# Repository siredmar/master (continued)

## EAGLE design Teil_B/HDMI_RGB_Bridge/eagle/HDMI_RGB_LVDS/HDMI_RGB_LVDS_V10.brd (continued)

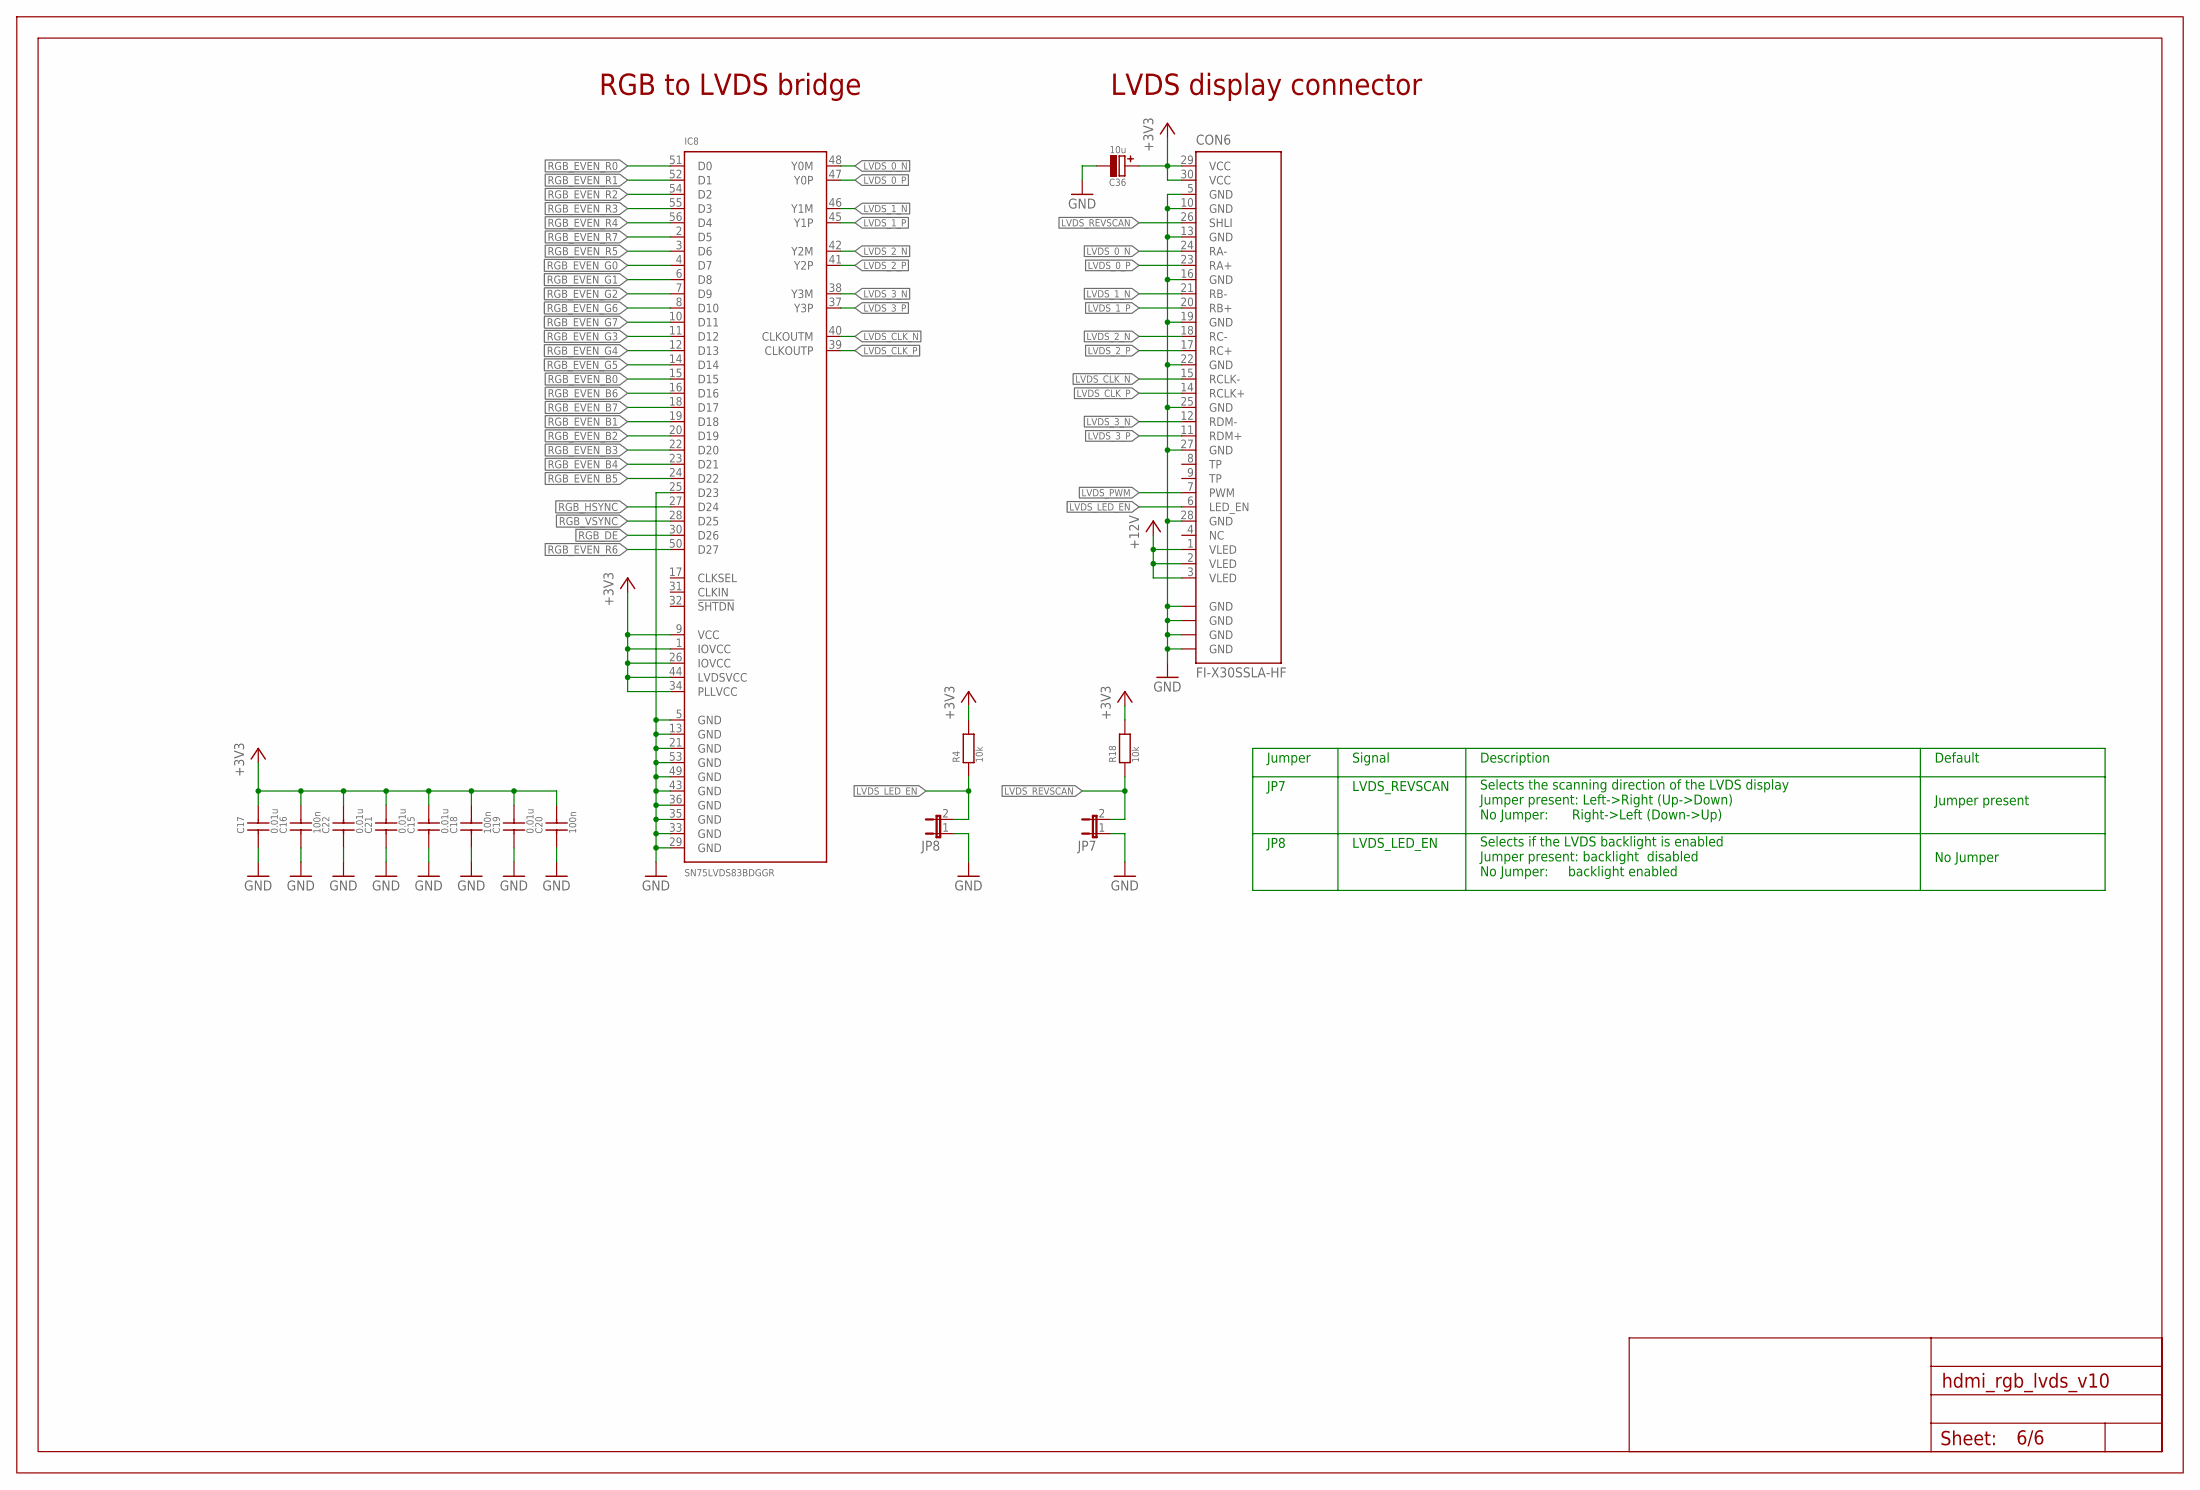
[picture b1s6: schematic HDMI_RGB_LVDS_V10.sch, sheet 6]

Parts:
C15, C17, C19, C21, C22: 0.01u; C0402
C16, C18, C20: 100n; C0402
C36: 10u; C_POL_4X4MM
CON6: FI-X30SSLA-HF
IC8: SN75LVDS83BDGGR; TSSOP-56
JP7, JP8: JUMPER2; JUMPER2_THROUGHHOLE
R4, R18: 10k; R0402
U$5: FRAME_A3_LANDSCAPE; FRAME

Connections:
+3V3: C15.2, C16.2, C17.2, C18.2, C19.2, C20.2, C21.2, C22.2, C36.+, CON6.29 (VCC), CON6.30 (VCC), IC8.1 (IOVCC), IC8.9 (VCC), IC8.26 (IOVCC), IC8.34 (PLLVCC), IC8.44 (LVDSVCC), R4.2, R18.2; also elsewhere on the board
+12V: CON6.1 (VLED), CON6.2 (VLED), CON6.3 (VLED); also elsewhere on the board
GND: C15.1, C16.1, C17.1, C18.1, C19.1, C20.1, C21.1, C22.1, C36.-, CON6.5 (GND), CON6.10 (GND), CON6.13 (GND), CON6.16 (GND), CON6.19 (GND), CON6.22 (GND), CON6.25 (GND), CON6.27 (GND), CON6.28 (GND), CON6.GND@1 (GND), CON6.GND@2 (GND), CON6.GND@3 (GND), CON6.GND@4 (GND), IC8.5 (GND), IC8.13 (GND), IC8.21 (GND), IC8.25 (D23), IC8.29 (GND), IC8.33 (GND), IC8.35 (GND), IC8.36 (GND), IC8.43 (GND), IC8.49 (GND), IC8.53 (GND), JP7.1, JP8.1; also elsewhere on the board
LVDS_0_N: CON6.24 (RA-), IC8.48 (Y0M)
LVDS_0_P: CON6.23 (RA+), IC8.47 (Y0P)
LVDS_1_N: CON6.21 (RB-), IC8.46 (Y1M)
LVDS_1_P: CON6.20 (RB+), IC8.45 (Y1P)
LVDS_2_N: CON6.18 (RC-), IC8.42 (Y2M)
LVDS_2_P: CON6.17 (RC+), IC8.41 (Y2P)
LVDS_3_N: CON6.12 (RDM-), IC8.38 (Y3M)
LVDS_3_P: CON6.11 (RDM+), IC8.37 (Y3P)
LVDS_CLK_N: CON6.15 (RCLK-), IC8.40 (CLKOUTM)
LVDS_CLK_P: CON6.14 (RCLK+), IC8.39 (CLKOUTP)
LVDS_LED_EN: CON6.6 (LED_EN), JP8.2, R4.1
LVDS_PWM: CON6.7 (PWM); also elsewhere on the board
LVDS_REVSCAN: CON6.26 (SHLI), JP7.2, R18.1
RGB_DE: IC8.30 (D26); also elsewhere on the board
RGB_EVEN_B0: IC8.15 (D15); also elsewhere on the board
RGB_EVEN_B1: IC8.19 (D18); also elsewhere on the board
RGB_EVEN_B2: IC8.20 (D19); also elsewhere on the board
RGB_EVEN_B3: IC8.22 (D20); also elsewhere on the board
RGB_EVEN_B4: IC8.23 (D21); also elsewhere on the board
RGB_EVEN_B5: IC8.24 (D22); also elsewhere on the board
RGB_EVEN_B6: IC8.16 (D16); also elsewhere on the board
RGB_EVEN_B7: IC8.18 (D17); also elsewhere on the board
RGB_EVEN_G0: IC8.4 (D7); also elsewhere on the board
RGB_EVEN_G1: IC8.6 (D8); also elsewhere on the board
RGB_EVEN_G2: IC8.7 (D9); also elsewhere on the board
RGB_EVEN_G3: IC8.11 (D12); also elsewhere on the board
RGB_EVEN_G4: IC8.12 (D13); also elsewhere on the board
RGB_EVEN_G5: IC8.14 (D14); also elsewhere on the board
RGB_EVEN_G6: IC8.8 (D10); also elsewhere on the board
RGB_EVEN_G7: IC8.10 (D11); also elsewhere on the board
RGB_EVEN_R0: IC8.51 (D0); also elsewhere on the board
RGB_EVEN_R1: IC8.52 (D1); also elsewhere on the board
RGB_EVEN_R2: IC8.54 (D2); also elsewhere on the board
RGB_EVEN_R3: IC8.55 (D3); also elsewhere on the board
RGB_EVEN_R4: IC8.56 (D4); also elsewhere on the board
RGB_EVEN_R5: IC8.3 (D6); also elsewhere on the board
RGB_EVEN_R6: IC8.50 (D27); also elsewhere on the board
RGB_EVEN_R7: IC8.2 (D5); also elsewhere on the board
RGB_HSYNC: IC8.27 (D24); also elsewhere on the board
RGB_VSYNC: IC8.28 (D25); also elsewhere on the board

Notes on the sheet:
JP7
Jumper
Description
Signal
LVDS_REVSCAN
Selects if the LVDS backlight is enabled Jumper present: backlight disabled No Jumper: backlight enabled
JP8
LVDS_LED_EN
Selects the scanning direction of the LVDS display Jumper present: Left->Right (Up->Down) No Jumper: Right->Left (Down->Up)
Default
No Jumper
Jumper present
RGB to LVDS bridge
LVDS display connector

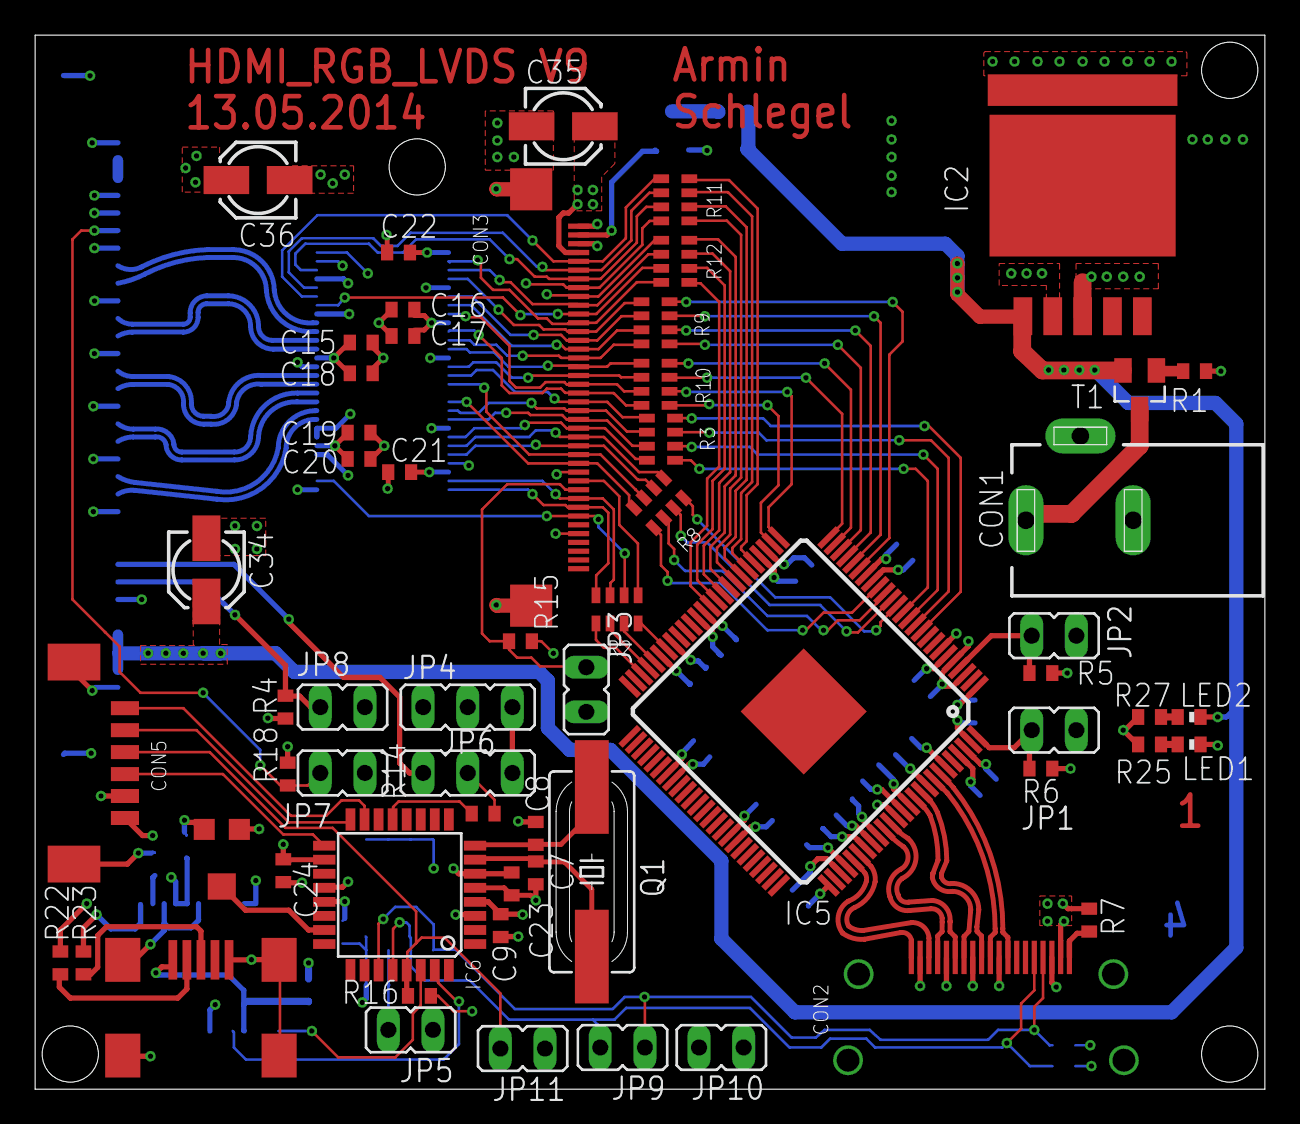
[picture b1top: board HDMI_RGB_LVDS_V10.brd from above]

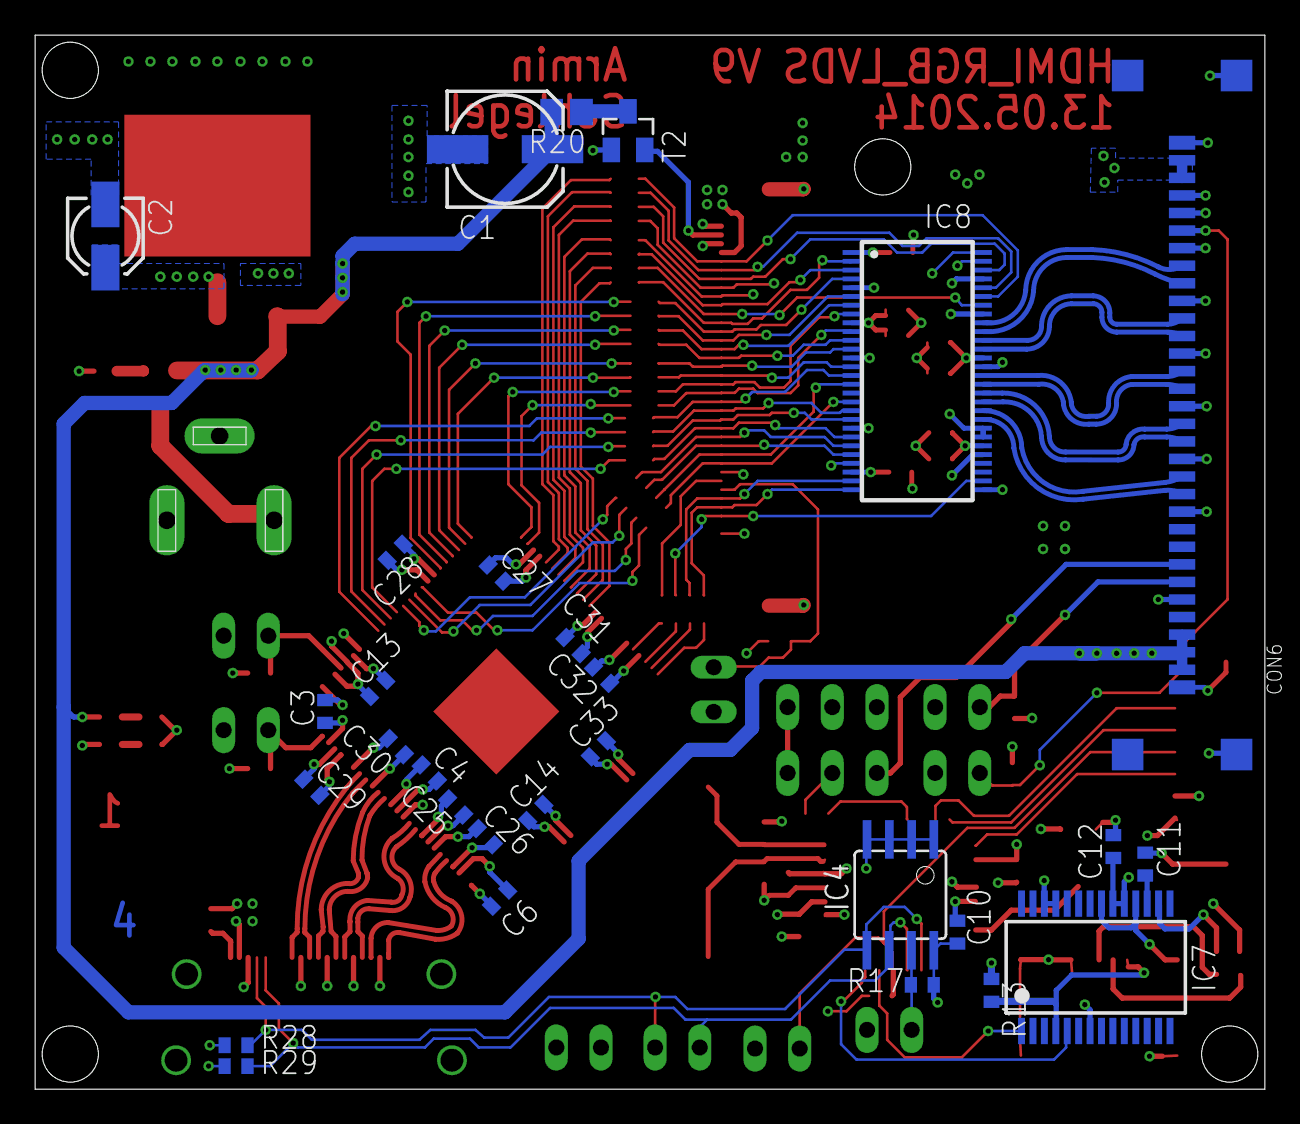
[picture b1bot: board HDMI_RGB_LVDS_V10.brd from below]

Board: 4 copper layers, 70.0 x 60.0 mm, 95 parts (29 on the bottom side), 111 nets.

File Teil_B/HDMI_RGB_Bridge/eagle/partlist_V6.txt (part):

Partlist

Exported from HDMI_RGB_LVDS_fertig_V6.sch at 4/28/14 9:10 AM

EAGLE Version 6.3.0 Copyright (c) 1988-2012 CadSoft

Assembly variant: 

Part     Value                Device                        Package              Library           Sheet

C1       100u                 RSS1C101MCN1GS                C_POL_6X6MM          SchlegelAr_Master 3
C2       10u                  C_POL4X4MM                    C_POL_4X4MM          SchlegelAr_Master 3
C3       100n                 C_SMD0402                     C0402                SchlegelAr_Master 4
C4       100n                 C_SMD0402                     C0402                SchlegelAr_Master 4
C6       100n                 C_SMD0402                     C0402                SchlegelAr_Master 4
C7       22p                  C_SMD0402                     C0402                SchlegelAr_Master 5
C8       22p                  C_SMD0402                     C0402                SchlegelAr_Master 5
C9       100n                 C_SMD0402                     C0402                SchlegelAr_Master 5
C10      100n                 C_SMD0402                     C0402                SchlegelAr_Master 5
C11      100n                 C_SMD0402                     C0402                SchlegelAr_Master 5
C12      100n                 C_SMD0402                     C0402                SchlegelAr_Master 5
C13      100n                 C_SMD0402                     C0402                SchlegelAr_Master 4
C14      100n                 C_SMD0402                     C0402                SchlegelAr_Master 4
C15      0.01u                C_SMD0402                     C0402                SchlegelAr_Master 6
C16      100n                 C_SMD0402                     C0402                SchlegelAr_Master 6
C17      0.01u                C_SMD0402                     C0402                SchlegelAr_Master 6
C18      100n                 C_SMD0402                     C0402                SchlegelAr_Master 6
C19      0.01u                C_SMD0402                     C0402                SchlegelAr_Master 6
C20      100n                 C_SMD0402                     C0402                SchlegelAr_Master 6
C21      0.01u                C_SMD0402                     C0402                SchlegelAr_Master 6
C22      0.01u                C_SMD0402                     C0402                SchlegelAr_Master 6
C23      100n                 C_SMD0402                     C0402                SchlegelAr_Master 5
C24      100n                 C_SMD0402                     C0402                SchlegelAr_Master 5
C25      100n                 C_SMD0402                     C0402                SchlegelAr_Master 4
C26      100n                 C_SMD0402                     C0402                SchlegelAr_Master 4
C27      100n                 C_SMD0402                     C0402                SchlegelAr_Master 4
C28      100n                 C_SMD0402                     C0402                SchlegelAr_Master 4
C29      100n                 C_SMD0402                     C0402                SchlegelAr_Master 4
C30      100n                 C_SMD0402                     C0402                SchlegelAr_Master 4
C31      100n                 C_SMD0402                     C0402                SchlegelAr_Master 4
C32      100n                 C_SMD0402                     C0402                SchlegelAr_Master 4
C33      100n                 C_SMD0402                     C0402                SchlegelAr_Master 4
C34      10u                  C_POL4X4MM                    C_POL_4X4MM          SchlegelAr_Master 4
C35      10u                  C_POL4X4MM                    C_POL_4X4MM          SchlegelAr_Master 4
C36      10u                  C_POL4X4MM                    C_POL_4X4MM          SchlegelAr_Master 6
CON1     KLDX-0202-A-LT       KLDX-0202-A-LT                KLDX-0202-A-LT       SchlegelAr_Master 3
CON2     FCI-10029449-111RLF  FCI-10029449-111RLF           FCI-10029449-111RLF  SchlegelAr_Master 4
CON3     XF2M-4015-1A         XF2M-4015-1A                  XF2M-4015-1A         SchlegelAr_Master 4
CON4     FCI-10033526-N3212LF FCI-10033526-N3212LF          FCI-10033526-N3212LF SchlegelAr_Master 5
CON5     MOLEX-53261-0671     MOLEX-53261-0671              MOLEX-53261-0671     SchlegelAr_Master 5
CON6     FI-X30SSLA-HF        FI-X30SSLA-HF                 FI-X30SSLA-HF        SchlegelAr_Master 6
IC2      WPMDL1300331BD       WPMDL1300331BD                TO263-5              SchlegelAr_Master 3
IC4      AT24C01C-SSHM-B      AT24C01C-SSHM-B               SOIC8                SchlegelAr_Master 5
IC5      TFP401APZP           TFP401APZP                    HTQFP-100            SchlegelAr_Master 4
IC6      ATMEGA88PA           ATMEGA48A-AU                  TQFP32               SchlegelAr_Master 5
IC7      FT232RL              FT232RL                       SSOP28               SchlegelAr_Master 5
IC8      SN75LVDS83BDGGR      SN75LVDS83BDGGR               TSSOP-56             SchlegelAr_Master 6
JP1      JUMPER2              JUMPER2                       JUMPER2_THROUGHHOLE  SchlegelAr_Master 4
JP2      JUMPER2              JUMPER2                       JUMPER2_THROUGHHOLE  SchlegelAr_Master 4
JP3      JUMPER2              JUMPER2                       JUMPER2_THROUGHHOLE  SchlegelAr_Master 4
JP4      JUMPER3              JUMPER3                       JUMPER3_THROUGHHOLE  SchlegelAr_Master 4
JP5                           JUMPER2                       JUMPER2_THROUGHHOLE  SchlegelAr_Master 5
JP6      JUMPER3              JUMPER3                       JUMPER3_THROUGHHOLE  SchlegelAr_Master 5
JP7                           JUMPER2                       JUMPER2_THROUGHHOLE  SchlegelAr_Master 6
JP8                           JUMPER2                       JUMPER2_THROUGHHOLE  SchlegelAr_Master 6
JP9      JUMPER2              JUMPER2                       JUMPER2_THROUGHHOLE  SchlegelAr_Master 5
JP10     JUMPER2              JUMPER2                       JUMPER2_THROUGHHOLE  SchlegelAr_Master 5
JP11                          JUMPER2                       JUMPER2_THROUGHHOLE  SchlegelAr_Master 5
LED1                          LED0402                       LED0402              SchlegelAr_Master 3
LED2                          LED0402                       LED0402              SchlegelAr_Master 3
Q1       ATS073ASM-1          ATS073ASM-1                   HC49/USSM            SchlegelAr_Master 5
R1       100k                 R0402                         R0402                SchlegelAr_Master 3
R2       22R                  CTR-742C083220JP-4X22R-4X0603 R-ARRAY-4X0603       SchlegelAr_Master 4
R3       22R                  CTR-742C083220JP-4X22R-4X0603 R-ARRAY-4X0603       SchlegelAr_Master 4
R4       10k                  R0402                         R0402                SchlegelAr_Master 6
R5       10k                  R0402                         R0402                SchlegelAr_Master 4
R6       10k                  R0402                         R0402                SchlegelAr_Master 4
R7       10k                  R0402                         R0402                SchlegelAr_Master 4
R8       22R                  CTR-742C083220JP-4X22R-4X0603 R-ARRAY-4X0603       SchlegelAr_Master 4
R9       22R                  CTR-742C083220JP-4X22R-4X0603 R-ARRAY-4X0603       SchlegelAr_Master 4
R10      22R                  CTR-742C083220JP-4X22R-4X0603 R-ARRAY-4X0603       SchlegelAr_Master 4
R11      22R                  CTR-742C083220JP-4X22R-4X0603 R-ARRAY-4X0603       SchlegelAr_Master 4
R12      22R                  CTR-742C083220JP-4X22R-4X0603 R-ARRAY-4X0603       SchlegelAr_Master 4
R13      10k                  R0402                         R0402                SchlegelAr_Master 5
R14      22R                  R0402                         R0402                SchlegelAr_Master 5
R15      10k                  R0402                         R0402                SchlegelAr_Master 4
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
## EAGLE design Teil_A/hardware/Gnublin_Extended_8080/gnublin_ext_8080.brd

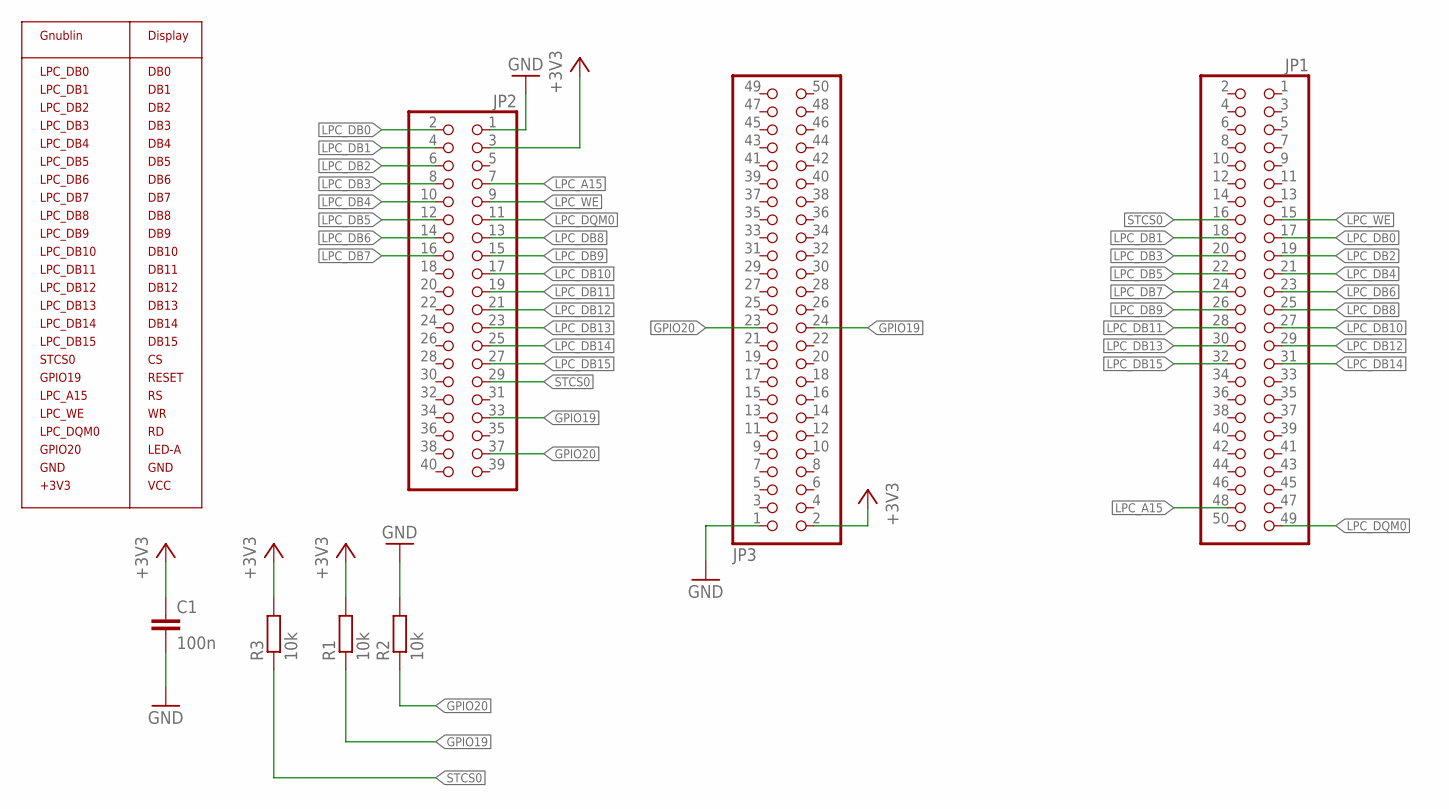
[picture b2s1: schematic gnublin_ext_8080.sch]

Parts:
C1: 100n; C0805
JP1, JP3: PINHD-2X25_2.54-SMD; 2X25SMD
JP2: PINHD-2X20; 2X20
R1, R2, R3: 10k; R0603

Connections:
+3V3: C1.1, JP2.3, JP3.2, R1.2, R3.2
GND: C1.2, JP2.1, JP3.1, R2.2
GPIO19: JP2.33, JP3.24, R1.1
GPIO20: JP2.37, JP3.23, R2.1
LPC_A15: JP1.48, JP2.7
LPC_DB0: JP1.17, JP2.2
LPC_DB1: JP1.18, JP2.4
LPC_DB2: JP1.19, JP2.6
LPC_DB3: JP1.20, JP2.8
LPC_DB4: JP1.21, JP2.10
LPC_DB5: JP1.22, JP2.12
LPC_DB6: JP1.23, JP2.14
LPC_DB7: JP1.24, JP2.16
LPC_DB8: JP1.25, JP2.13
LPC_DB9: JP1.26, JP2.15
LPC_DB10: JP1.27, JP2.17
LPC_DB11: JP1.28, JP2.19
LPC_DB12: JP1.29, JP2.21
LPC_DB13: JP1.30, JP2.23
LPC_DB14: JP1.31, JP2.25
LPC_DB15: JP1.32, JP2.27
LPC_DQM0: JP1.49, JP2.11
LPC_WE: JP1.15, JP2.9
STCS0: JP1.16, JP2.29, R3.1

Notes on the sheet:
DB0
DB1
DB2
DB3
DB4
DB5
DB6
DB7
RESET
LED-A
GND
VCC
+3V3
Gnublin
Display
DB8
DB9
DB10
DB11
DB12
DB13
DB14
DB15
LPC_DB0
LPC_DB1
LPC_DB2
LPC_DB3
LPC_DB4
LPC_DB5
LPC_DB6
LPC_DB7
LPC_DB8
LPC_DB9
LPC_DB10
LPC_DB11
LPC_DB12
LPC_DB13
LPC_DB14
LPC_DB15
STCS0

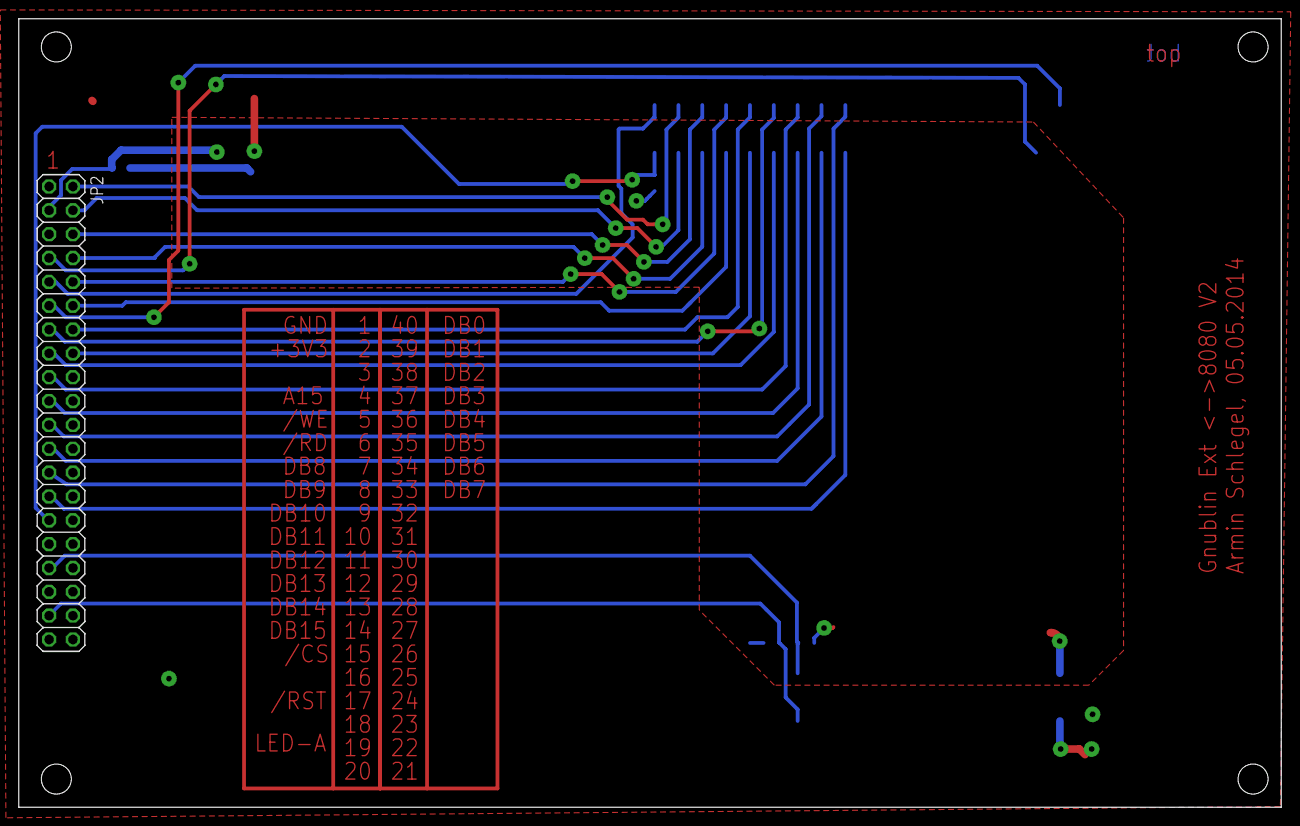
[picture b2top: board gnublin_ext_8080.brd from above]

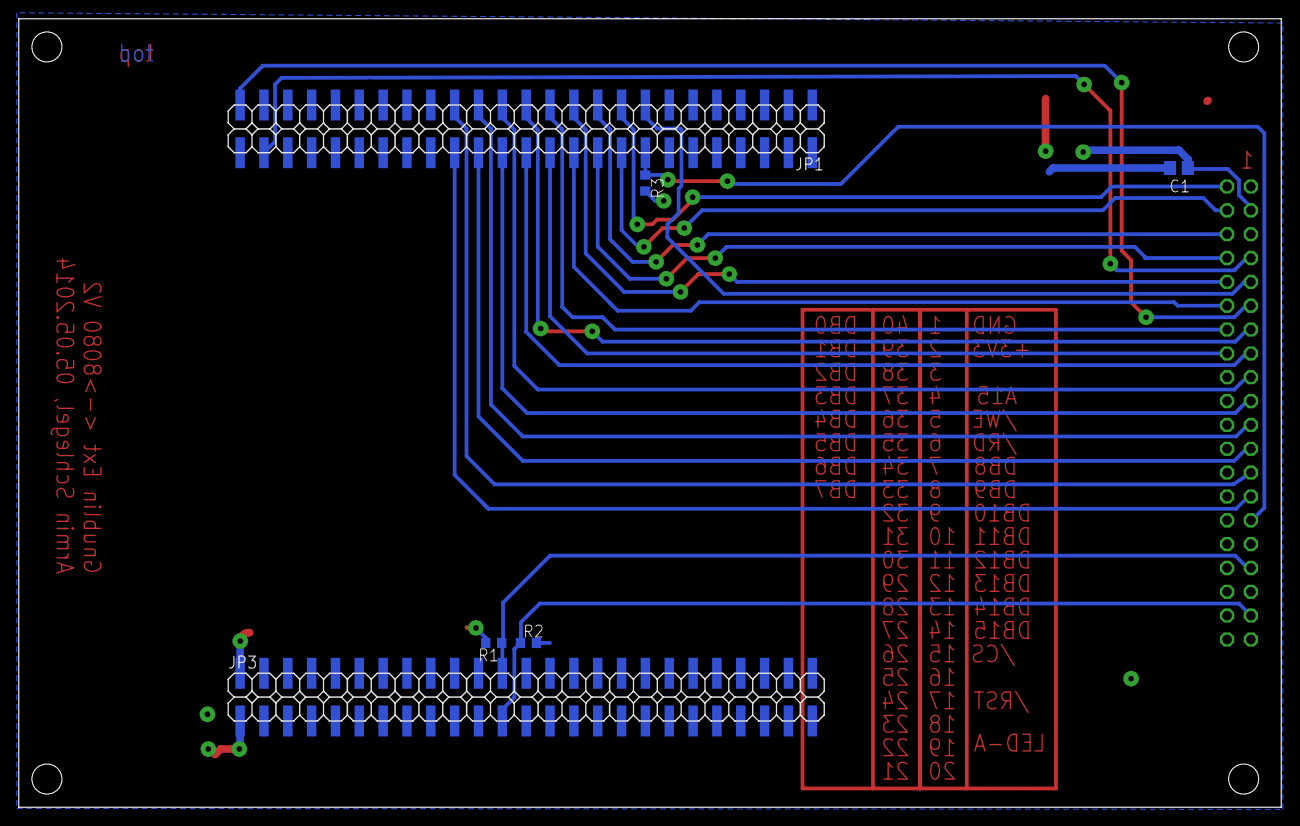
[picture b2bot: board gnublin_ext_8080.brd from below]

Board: 2 copper layers, 134.5 x 84.0 mm, 7 parts (6 on the bottom side), 24 nets.

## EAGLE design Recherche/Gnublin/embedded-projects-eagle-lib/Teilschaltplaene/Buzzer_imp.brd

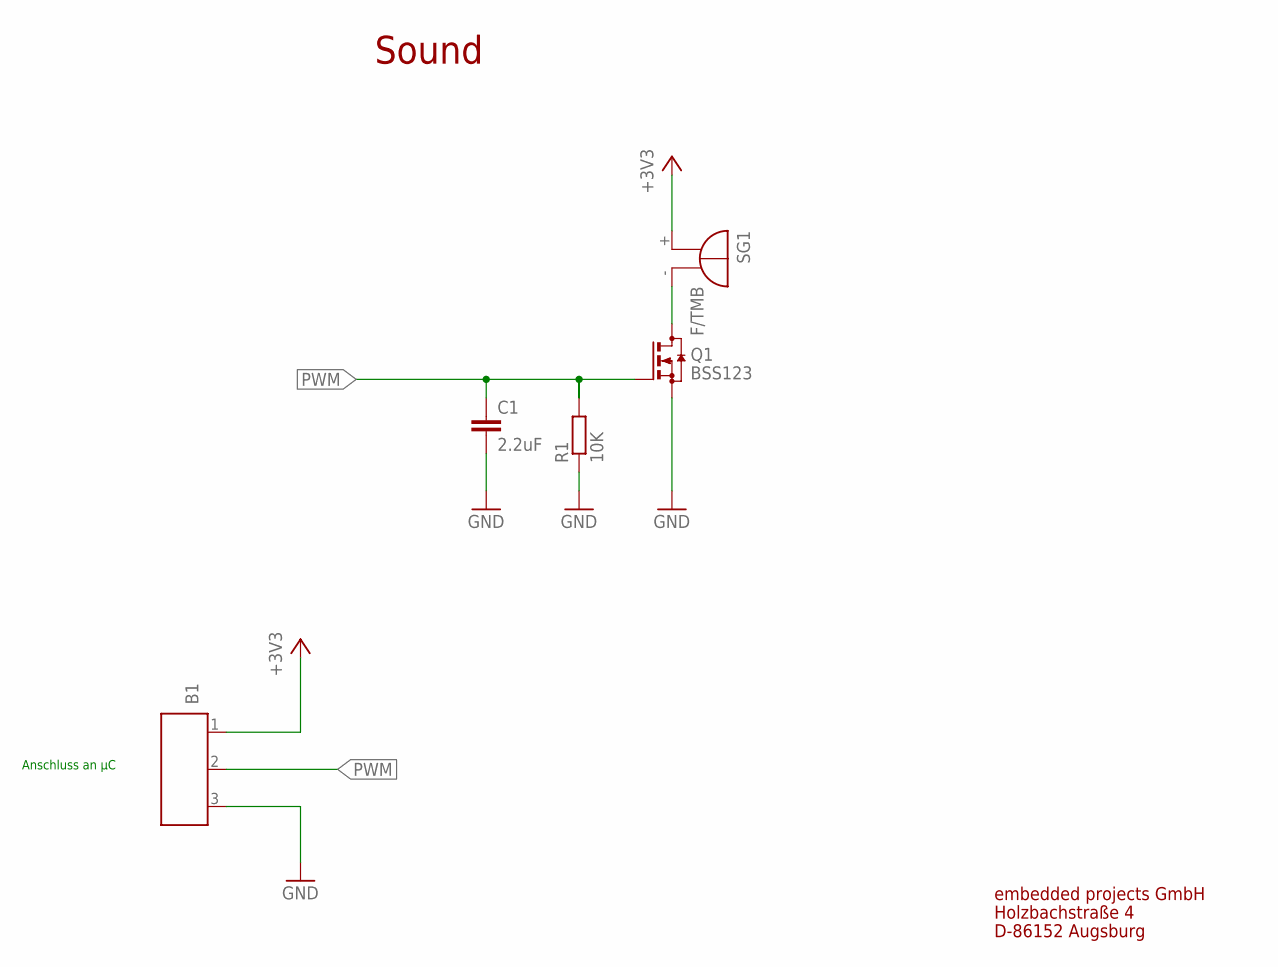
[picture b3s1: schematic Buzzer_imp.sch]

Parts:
B1: MESSFUEHLER_3
C1: 2.2uF; C0805
Q1: BSS123; SOT-23
R1: 10K; R0805
SG1: F/TMB

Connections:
+3V3: B1.1, SG1.+
GND: B1.3, C1.2, Q1.2 (S), R1.1
unnamed: Q1.3 (D), SG1.-
PWM: B1.2, C1.1, Q1.1 (G), R1.2

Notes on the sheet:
Sound
Anschluss an µC
embedded projects GmbH
Holzbachstraße 4
D-86152 Augsburg

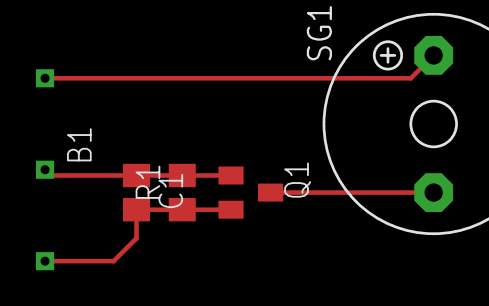
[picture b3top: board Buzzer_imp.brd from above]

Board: 2 copper layers, 5 parts (0 on the bottom side), 4 nets.

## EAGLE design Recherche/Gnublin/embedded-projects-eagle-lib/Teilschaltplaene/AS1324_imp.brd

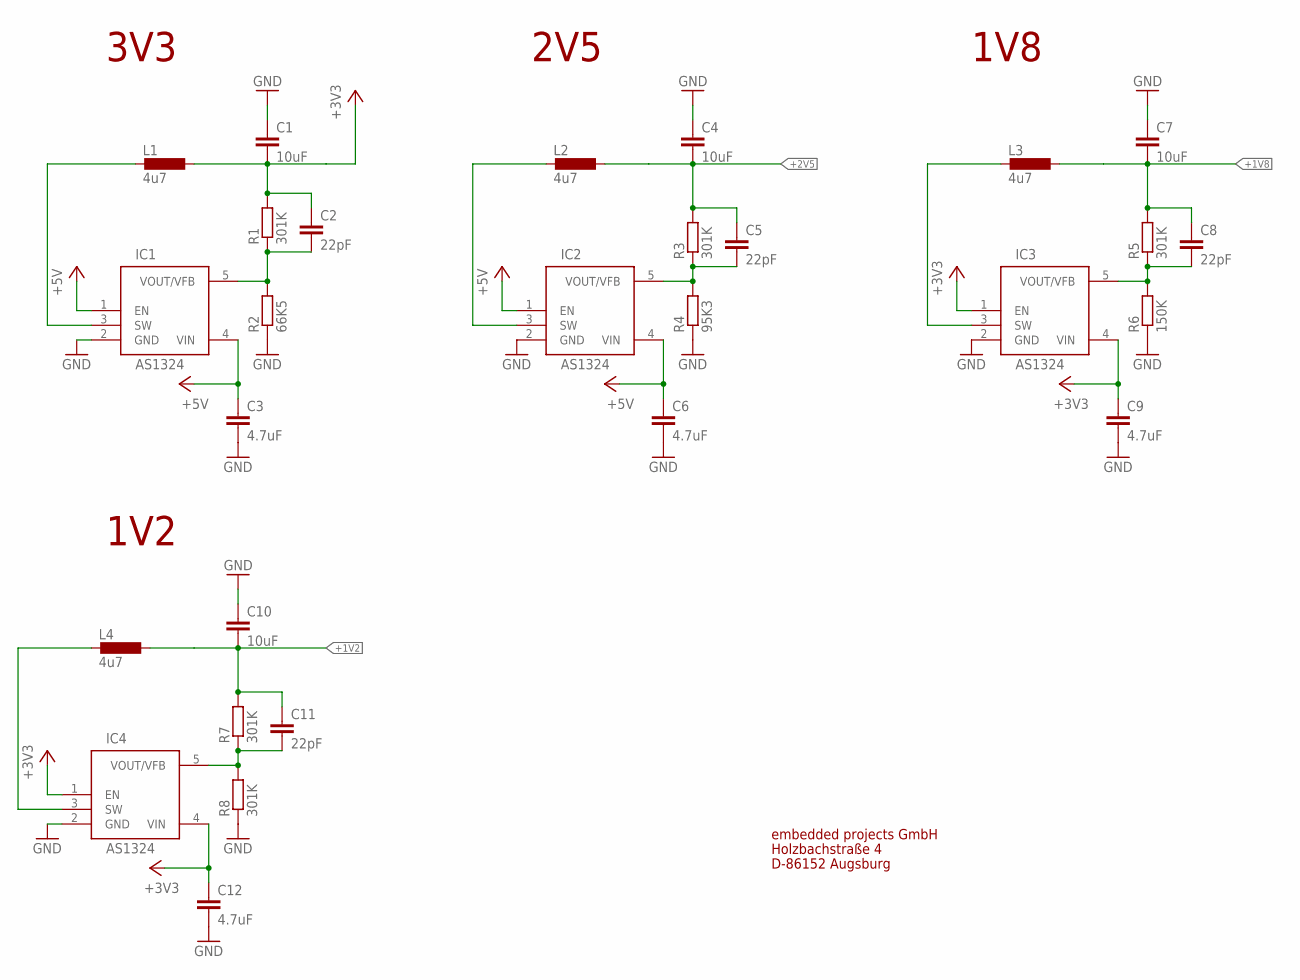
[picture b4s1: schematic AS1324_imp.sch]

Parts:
C1, C4, C7, C10: 10uF; C0805
C2, C5, C8, C11: 22pF; C0805
C3, C6, C9, C12: 4.7uF; C0805
IC1, IC2, IC3, IC4: AS1324; TSOT23
L1, L2, L3, L4: 4u7; PSU3014
R1, R3, R5, R7, R8: 301K; R0805
R2: 66K5; R0805
R4: 95K3; R0805
R6: 150K; R0805

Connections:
+1V2: C10.2, C11.1, L4.2, R7.2
+1V8: C7.2, C8.1, L3.2, R5.2
+2V5: C4.2, C5.1, L2.2, R3.2
+3V3: C1.2, C2.1, C9.1, C12.1, IC3.1 (EN), IC3.4 (VIN), IC4.1 (EN), IC4.4 (VIN), L1.2, R1.2
+5V: C3.1, C6.1, IC1.1 (EN), IC1.4 (VIN), IC2.1 (EN), IC2.4 (VIN)
GND: C1.1, C3.2, C4.1, C6.2, C7.1, C9.2, C10.1, C12.2, IC1.2 (GND), IC2.2 (GND), IC3.2 (GND), IC4.2 (GND), R2.1, R4.1, R6.1, R8.1
unnamed: IC4.3 (SW), L4.1
unnamed: IC3.3 (SW), L3.1
unnamed: C11.2, IC4.5 (VOUT/VFB), R7.1, R8.2
unnamed: C8.2, IC3.5 (VOUT/VFB), R5.1, R6.2
unnamed: IC1.3 (SW), L1.1
unnamed: C2.2, IC1.5 (VOUT/VFB), R1.1, R2.2
unnamed: IC2.3 (SW), L2.1
unnamed: C5.2, IC2.5 (VOUT/VFB), R3.1, R4.2

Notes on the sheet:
3V3
1V2
embedded projects GmbH
Holzbachstraße 4
D-86152 Augsburg
1V8
2V5

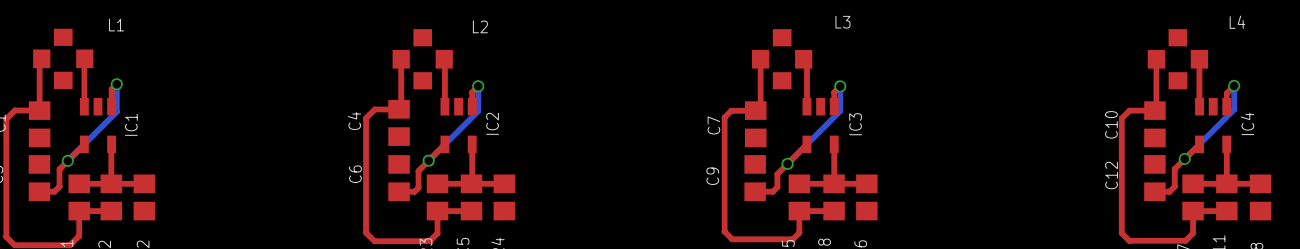
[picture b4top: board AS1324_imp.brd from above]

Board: 4 copper layers, 28 parts (0 on the bottom side), 14 nets.

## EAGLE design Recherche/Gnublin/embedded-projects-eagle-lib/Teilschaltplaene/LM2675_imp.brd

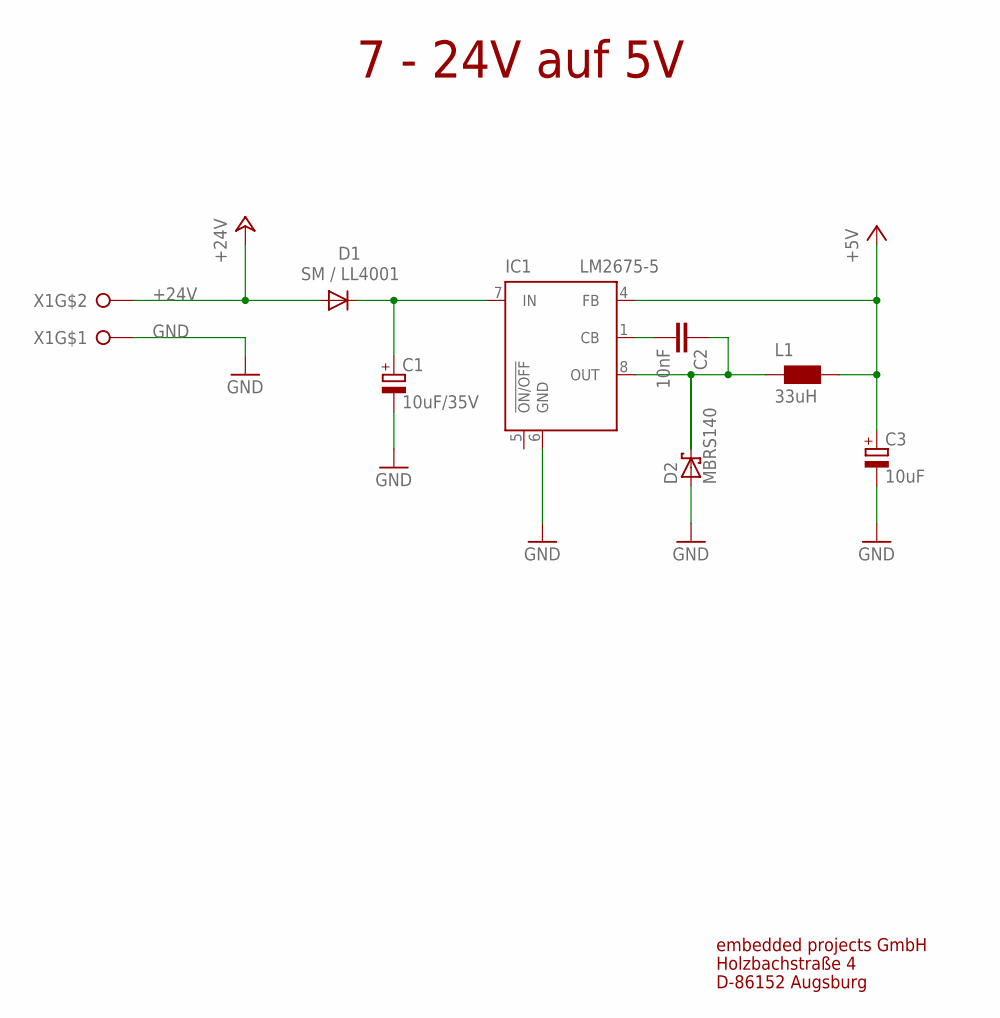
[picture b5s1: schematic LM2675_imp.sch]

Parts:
C1: 10uF/35V; PANASONIC_C; FARNELL 9697012
C2: 10nF; C0805
C3: 10uF; D/7343-31R
D1: SM / LL4001; MINIMELF; FARNELL 7355521
D2: MBRS140; SMB
IC1: LM2675-5; SO-8; FARNELL 9489746
L1: 33uH; WE-PD_S/M; FARNELL 744778133
X1: CON-WAGO508_W237-02; W237-132

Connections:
+5V: C3.+, IC1.4 (FB), L1.1 (2)
+24V: D1.A, X1.2
GND: C1.-, C3.-, D2.A, IC1.6 (GND), X1.1
unnamed: C1.+, D1.C, IC1.7 (IN)
unnamed: C2.2, IC1.1 (CB)
OUT: C2.1, D2.C, IC1.8 (OUT), L1.2 (1)

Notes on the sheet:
7 - 24V auf 5V
embedded projects GmbH
Holzbachstraße 4
D-86152 Augsburg

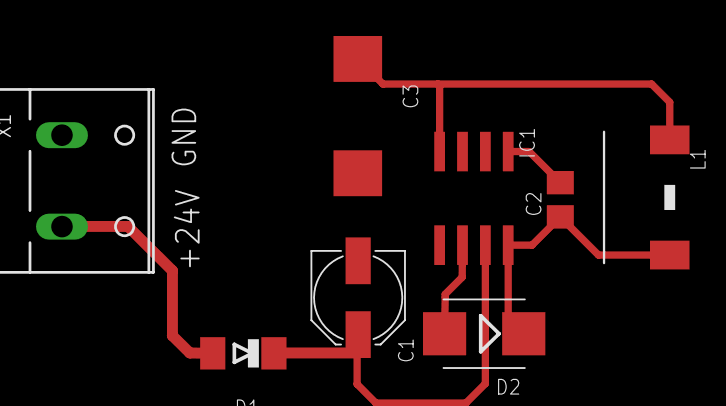
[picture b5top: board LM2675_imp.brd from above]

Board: 2 copper layers, 8 parts (0 on the bottom side), 6 nets.
